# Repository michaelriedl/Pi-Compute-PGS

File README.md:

# Pi-Compute-PGS
Portable gaming system based on the Raspberry Pi Compute module

I took this project as far as I possibly could but ran out of steam. I figured I would open source it so other people can take it up if they like. The major revisions I was facing are as follows:

1. The buttons need to be moved further away from the screen.
I designed the board independent of designing the enclosure which was a huge mistake. There is not enough clearance around the screen to accomodate a correctly sized button.
2. I ordered the wrong battery IC and ended up frying a prototype board trying to simultaneosy play and charge the PGS.
3. Stereo out
4. HDMI out
5. On-board WiFi

This board was designed in a 4.x version of KiCad and has not been updated to 5.0+ so I'm not sure how it will behave.

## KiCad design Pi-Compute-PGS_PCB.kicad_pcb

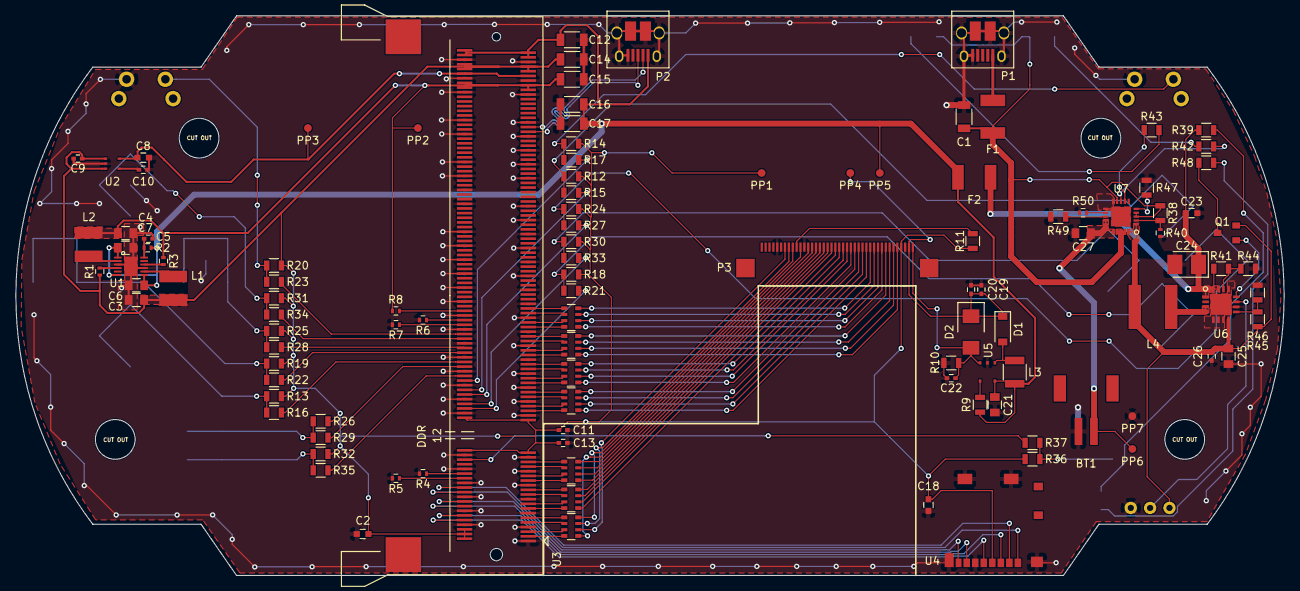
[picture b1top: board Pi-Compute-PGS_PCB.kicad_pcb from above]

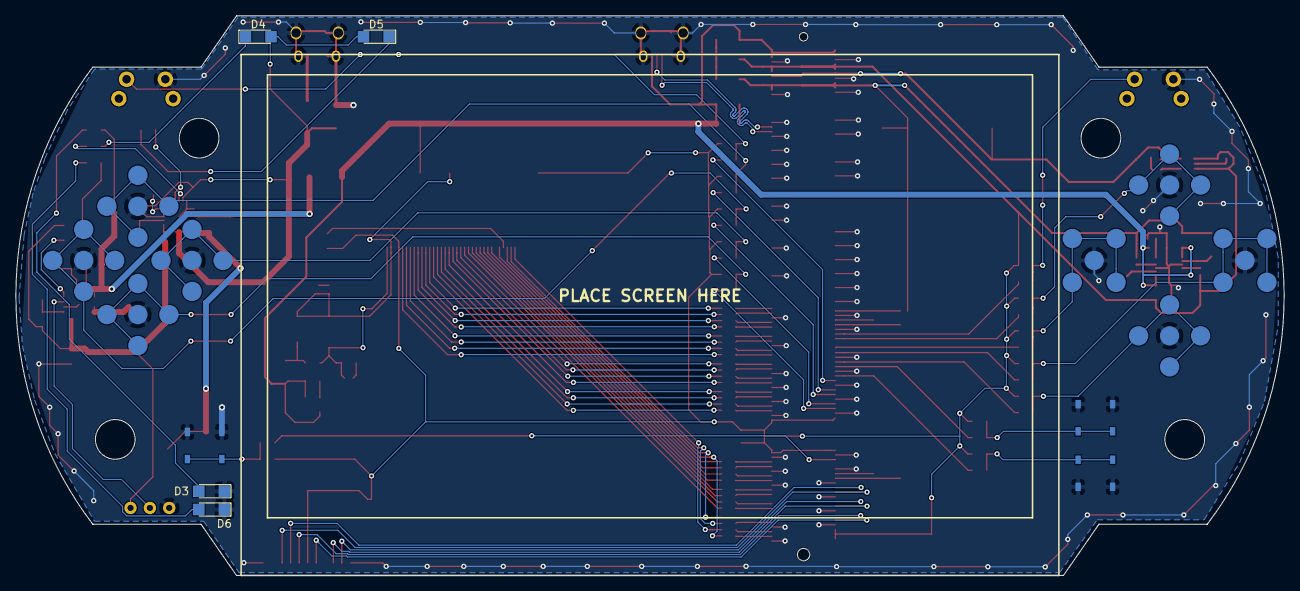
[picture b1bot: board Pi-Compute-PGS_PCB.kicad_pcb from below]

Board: 2 copper layers, 163.6 x 72.2 mm, 129 parts (15 on the bottom side), 132 nets.

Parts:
BT1: JST 2-PH; JST_2_PH
C1, C12, C14, C15, C16, C17: 47uF; C_1206
C2, C8, C18: 4.7uF; C_0603
C3, C4, C6, C7, C21, C25, C27: 10uF; C_0805
C5, C10, C26: 100nF; C_0402
C9, C11, C13, C19, C20: 1uF; C_0402
C22: 0.1uF; C_0402
C23: 2.2uF; C_0603
C24: 100uF; CP_Tantalum_Case-B_EIA-3528-21_Reflow
D1: MBR0540; D_SOD-123
D2: SMAZ24-TP
D3: Blue; LED_1206
D4: Orange; LED_1206
D5: Green; LED_1206
D6: Red; LED_1206
F1, F2: MF-MSMF200
L1, L2: 4.7uH; SRN4018-4R7M
L3: BRL3225T150K; C_1210
L4: 6.8uH; ASPI-0615FS-6R8M-T2
P1, P2: USB_OTG; USB_Micro-B_10103594-0001LF
P3: 40_Pin_LCD_Out; LCD_Molex_Connector
PP1, PP2, PP3, PP4, PP5, PP6, PP7: Test_Point
Q1: MMUN2133LT1G
R1, R3: 0R; R_0402
R2, R4, R5, R6, R7, R8, R40, R50: 100k; R_0402
R9, R11, R12, R13, R14, R18, R19, R20, R24, R25, R26, R30, R31, R32, R36: 10k; R_0805
R10: 12; R_0805
R15, R16, R17, R21, R22, R23, R27, R28, R29, R33, R34, R35, R37, R39, R42, R43, R48, R49: 1k; R_0805
R38: 270k; R_0805
R41, R45: 1.87M; R_0805
R44: 200k; R_0805
R46: 340k; R_0805
R47: 15k; R_0805
RP1, RP2, RP3, RP4, RP5, RP6, RP7: 33 R_PACK4; R_Array_Convex_4x0603
SW1, SW2: SW_PUSH_SMALL_H; Tact-switch_right_thru_hole
SW3, SW4, SW5, SW6, SW7, SW8, SW9, SW10: SW_PUSH_SMALL_H; Snapdome_SW
SW11, SW12, SW13: SW_PUSH_SMALL_H; E-SW_SMD
U1: PAM2306AYPKE
U2: AP7115-25SEG; AP7115-25SEG-7
U3: DDR2_SODIMM_CM_3_Lite; Socket_SODIMM_DDR2
U4: 1040310811; uSD_1040310811
U5: FAN5333BSX
U6: TPS61090RSAR
U7: MCP73871
U8: SPDT_switch; spdt_switch_MHSS1105

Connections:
1V8: C4.1, C15.1, L2.2, PP2.1, R3.1, R8.2, U3.183, U3.184, U3.185, U3.186
3V3: C2.1, C3.1, C9.1, C11.1, C13.1, C14.1, C18.1, L1.2, P3.4, PP1.1, R1.1, R11.1, R12.2, R13.2, R14.2, R18.2, R19.2, R20.2, R24.2, R25.2, R26.2, R30.2, R31.2, R32.2, R36.2, U2.1, U2.3, U3.2, U3.4, U3.6, U3.39, U3.40, U3.41, U3.42, U3.191, U3.192, U3.193, U3.194, U4.4
5V: C6.1, C7.1, C12.1, C16.1, C17.1, C21.1, F2.1, L3.1, P2.1, PP5.1, R2.1, R9.2, U1.1, U1.6, U1.7, U3.197, U3.198, U3.199, U3.200, U5.5
24V: C19.2, C20.2, D1.1, D2.1, P3.2, PP4.1
A: R16.2, U3.66
A_IN: R13.1, R16.1, SW10.1
B: R22.2, U3.70
B0: RP5.8, U3.15
B1: RP5.7, U3.17
B2: RP5.6, U3.21
B3: RP5.5, U3.23
B4: RP6.8, U3.27
B5: RP6.7, U3.29
B6: RP6.6, U3.33
B7: RP6.5, U3.35
B_IN: R19.1, R22.1, SW7.1
CM_VDAC: C8.1, PP3.1, U2.5, U3.189, U3.190
DE: RP7.7, U3.5
DOWN: R21.2, U3.46
DOWN_IN: R18.1, R21.1, SW9.1
EN_PWR: U6.11, U8.2
G0: RP3.8, U3.45
G1: RP3.7, U3.47
G2: RP3.6, U3.51
G3: RP3.5, U3.53
G4: RP4.8, U3.57
G5: RP4.7, U3.59
G6: RP4.6, U3.63
G7: RP4.5, U3.65
GND: BT1.2, C1.2, C2.2, C3.2, C4.2, C5.2, C6.2, C7.2, C8.2, C9.2, C10.2, C11.2, C12.2, C13.2, C14.2, C15.2, C16.2, C17.2, C18.2, C19.1, C20.1, C21.2, C22.2, C23.2, C24.2, C25.2, C26.2, C27.2, D3.1, D6.1, P1.5, P1.6, P2.5, P2.6, P3.3, P3.29, P3.36, PP7.1, R4.2, R5.2, R6.2, R7.2, R10.1, R40.2, R44.2, R46.2, R47.2, R49.2, R50.2, SW1.2, SW2.2, SW3.2, SW4.2, SW5.2, SW6.2, SW7.2, SW8.2, SW9.2, SW10.2, SW11.2, SW12.2, SW13.2, U1.3, U1.9, U1.13, U2.2, U3.1, U3.7, U3.8, U3.13, U3.14, U3.19, U3.20, U3.25, U3.26, U3.31, U3.32, U3.37, U3.38, U3.43, U3.44, U3.49, U3.50, U3.55, U3.56, U3.61, U3.62, U3.67, U3.68, U3.73, U3.74, U3.79, U3.80, U3.85, U3.86, U3.91, U3.92, U3.97, U3.98, U3.103, U3.104, U3.109, U3.110, U3.115, U3.116, U3.121, U3.122, U3.127, U3.133, U3.134, U3.139, U3.140, U3.145, U3.146, U3.151, U3.152, U3.157, U3.163, U3.164, U3.169, U3.170, U3.181, U3.182, U3.187, U3.188, U3.195, U3.196, U4.6, U4.11, U4.12, U4.13, U4.14, U5.2, U6.5, U6.6, U6.7, U6.10, U6.13, U6.17, U7.10, U7.11, U7.21, U8.1
HOME: R37.2, U3.36
HOME_IN: R36.1, R37.1, SW13.1
HSYNC: RP7.5, U3.11
LEDK: C22.1, D2.2, P3.1, R10.2, U5.3
LEFT: R27.2, U3.52
LEFT_IN: R24.1, R27.1, SW5.1
L_BUMP: R17.2, U3.58
L_BUMP_IN: R14.1, R17.1, SW1.1
unnamed: BT1.1, C27.1, PP6.1, U7.14, U7.15, U7.16
unnamed: C5.1, R2.2, U1.12
unnamed: C10.1, U2.4
unnamed: C23.1, C24.1, F2.2, R39.1, R41.1, U6.1, U6.15, U6.16
unnamed: D1.2, L3.2, U5.1
unnamed: D3.2, R39.2
unnamed: D4.1, R42.1
unnamed: D5.1, R43.1
unnamed: D6.2, R48.2
unnamed: F1.2, P1.1
unnamed: L1.1, U1.8
unnamed: L2.1, U1.2
unnamed: L4.2, U6.3, U6.4
unnamed: P3.5, RP1.1
unnamed: P3.6, RP1.2
unnamed: P3.7, RP1.3
unnamed: P3.8, RP1.4
unnamed: P3.9, RP2.1
unnamed: P3.10, RP2.2
unnamed: P3.11, RP2.3
unnamed: P3.12, RP2.4
unnamed: P3.13, RP3.1
unnamed: P3.14, RP3.2
unnamed: P3.15, RP3.3
unnamed: P3.16, RP3.4
unnamed: P3.17, RP4.1
unnamed: P3.18, RP4.2
unnamed: P3.19, RP4.3
unnamed: P3.20, RP4.4
unnamed: P3.21, RP5.1
unnamed: P3.22, RP5.2
unnamed: P3.23, RP5.3
unnamed: P3.24, RP5.4
unnamed: P3.25, RP6.1
unnamed: P3.26, RP6.2
unnamed: P3.27, RP6.3
unnamed: P3.28, RP6.4
unnamed: P3.30, RP7.1
unnamed: P3.31, R11.2
unnamed: P3.32, RP7.4
unnamed: P3.33, RP7.3
unnamed: P3.34, RP7.2
unnamed: Q1.1, U6.12
unnamed: Q1.3, R48.1
unnamed: R1.2, U1.4
unnamed: R3.2, U1.10
unnamed: R4.1, U3.30
unnamed: R5.1, U3.28
unnamed: R6.1, U3.84
unnamed: R7.1, U3.82
unnamed: R8.1, U3.88
unnamed: R9.1, U5.4
unnamed: R38.2, R40.1, U7.2
unnamed: R41.2, R44.1, U6.14
unnamed: R42.2, U7.8
unnamed: R43.2, U7.7
unnamed: R45.2, R46.1, U6.9
unnamed: R47.1, U7.5
unnamed: R49.1, U7.13
unnamed: R50.1, U7.12
ODCK: RP7.8, U3.3
PWR_IN: C1.1, D4.2, D5.2, F1.1, R38.1, U7.3, U7.4, U7.9, U7.17, U7.18, U7.19
R0: RP1.8, U3.69
R1: RP1.7, U3.71
R2: RP1.6, U3.75
R3: RP1.5, U3.77
R4: RP2.8, U3.81
R5: RP2.7, U3.83
R6: RP2.6, U3.87
R7: RP2.5, U3.89
RIGHT: R33.2, U3.48
RIGHT_IN: R30.1, R33.1, SW6.1
R_BUMP: R23.2, U3.78
R_BUMP_IN: R20.1, R23.1, SW2.1
SDX_CLK: U3.10, U4.5
SDX_CMD: U3.12, U4.3
SDX_D0: U3.16, U4.7
SDX_D1: U3.18, U4.8
SDX_D2: U3.22, U4.1
SDX_D3: U3.24, U4.2
SELECT: R35.2, U3.60
SELECT_IN: R32.1, R35.1, SW12.1
START: R29.2, U3.64
START_IN: R26.1, R29.1, SW11.1
UP: R15.2, U3.54
UP_IN: R12.1, R15.1, SW3.1
USB_D+: P2.3, U3.165
USB_D-: P2.2, U3.167
VBAT: C25.1, C26.1, L4.1, Q1.2, R45.1, U6.8, U7.1, U7.20, U8.3
VSYNC: RP7.6, U3.9
X: R28.2, U3.72
X_IN: R25.1, R28.1, SW8.1
Y: R34.2, U3.76
Y_IN: R31.1, R34.1, SW4.1

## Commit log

2020-01-09 Initial dump
